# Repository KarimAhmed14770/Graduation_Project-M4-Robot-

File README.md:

"# Graduation_Project-M4-Robot-"

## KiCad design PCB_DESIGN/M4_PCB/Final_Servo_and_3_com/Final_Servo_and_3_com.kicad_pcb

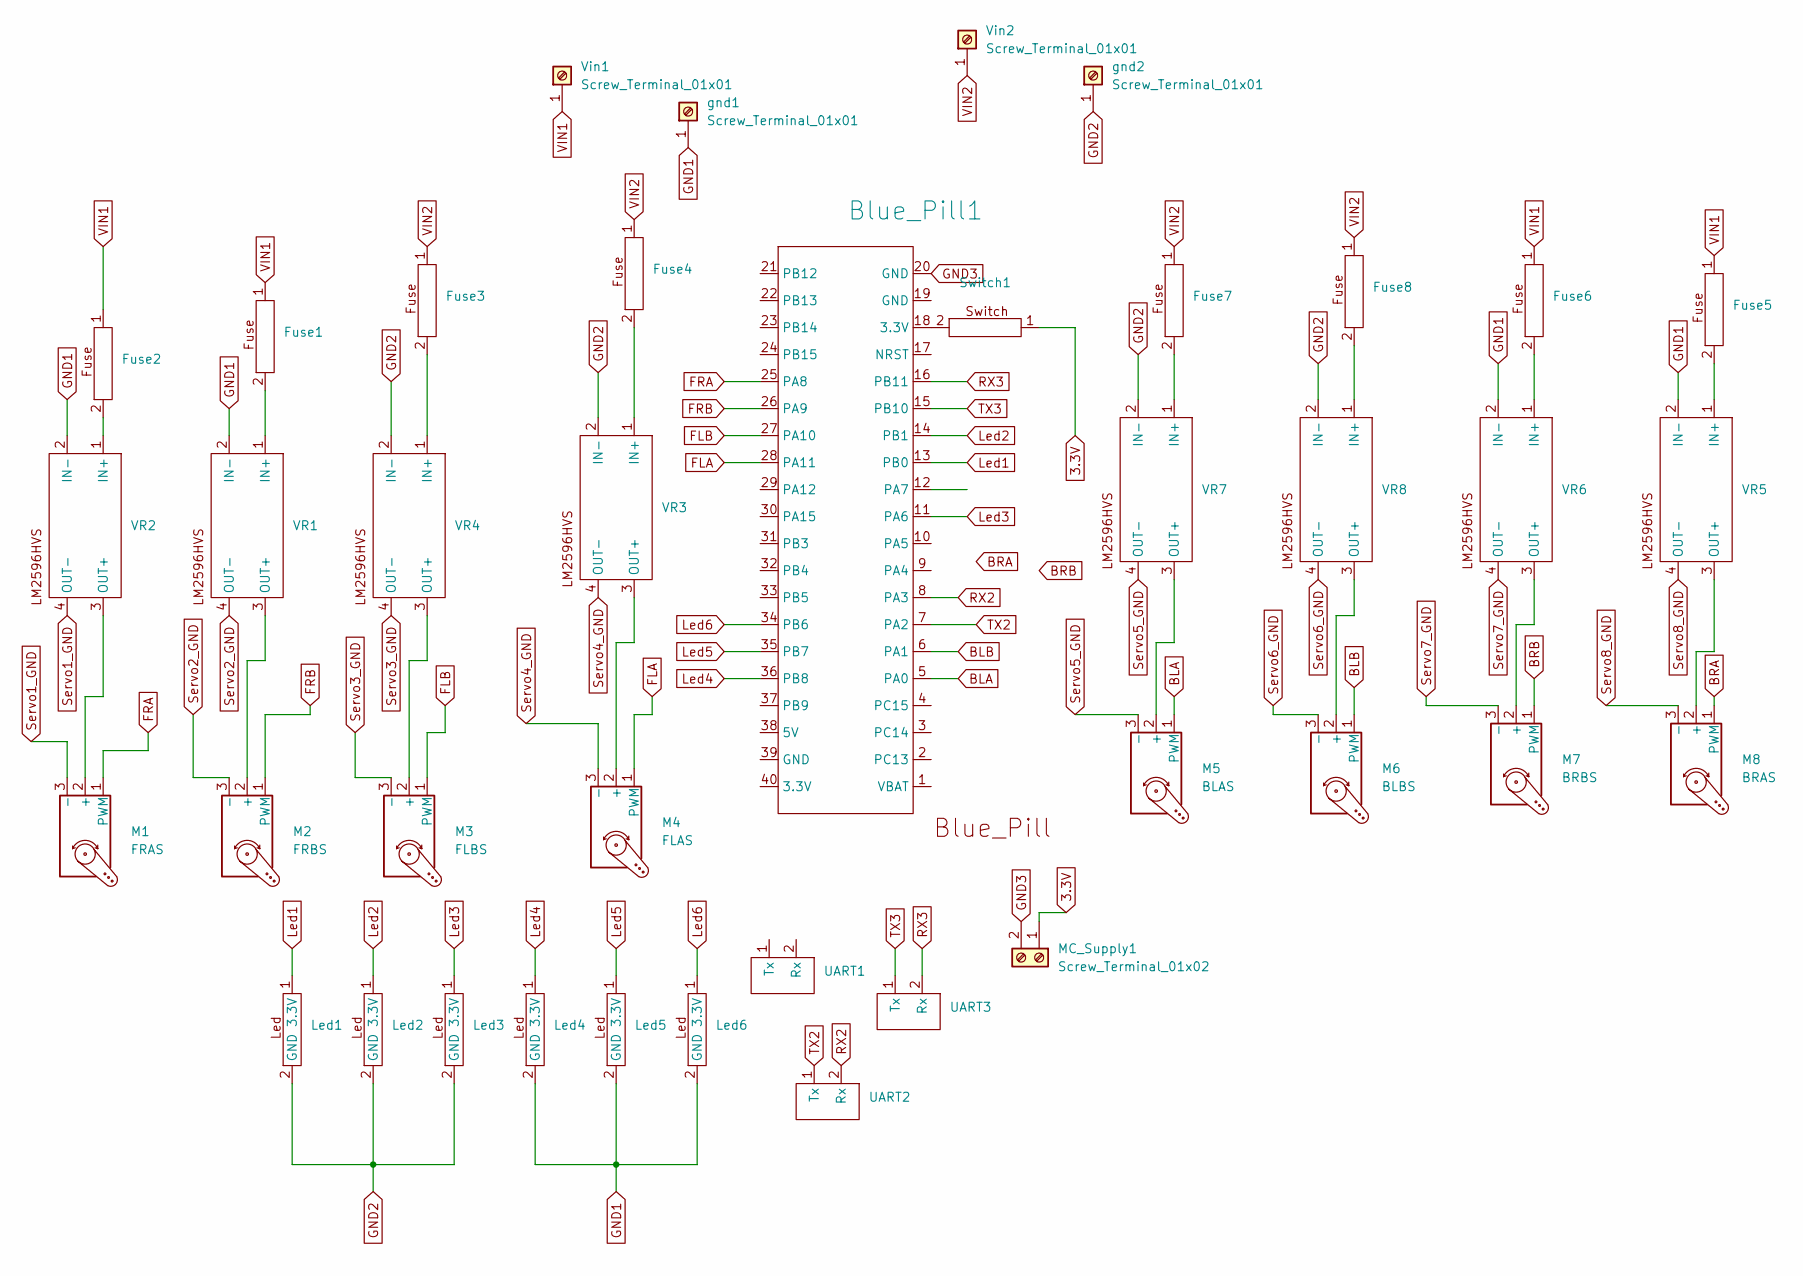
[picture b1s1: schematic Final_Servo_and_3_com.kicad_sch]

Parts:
Blue_Pill1: blue_pill
Fuse1, Fuse2, Fuse3, Fuse4, Fuse5, Fuse6, Fuse7, Fuse8: Fuse_Holder
Led1, Led2, Led3, Led4, Led5, Led6: LED
M1: FRAS; Servo
M2: FRBS; Servo
M3: FLBS; Servo
M4: FLAS; Servo
M5: BLAS; Servo
M6: BLBS; Servo
M7: BRBS; Servo
M8: BRAS; Servo
MC_Supply1: Screw_Terminal_01x02; Microcontrollers
Switch1: switch
UART1, UART2, UART3: communication
VR1, VR2, VR3, VR4, VR5, VR6, VR7, VR8: LM2596HVS
Vin1, Vin2: Screw_Terminal_01x01; one_terminal_VDD
gnd1, gnd2: Screw_Terminal_01x01; one_terminal_GND

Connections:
3.3V: MC_Supply1.1, Switch1.1
BLA: Blue_Pill1.5 (PA0), M5.1 (PWM)
BLB: Blue_Pill1.6 (PA1), M6.1 (PWM)
FLA: Blue_Pill1.28 (PA11), M4.1 (PWM)
FLB: Blue_Pill1.27 (PA10), M3.1 (PWM)
FRA: Blue_Pill1.25 (PA8), M1.1 (PWM)
FRB: Blue_Pill1.26 (PA9), M2.1 (PWM)
GND1: Led4.2 (GND), Led5.2 (GND), Led6.2 (GND), VR1.2 (IN-), VR2.2 (IN-), VR5.2 (IN-), VR6.2 (IN-), gnd1.1
GND2: Led1.2 (GND), Led2.2 (GND), Led3.2 (GND), VR3.2 (IN-), VR4.2 (IN-), VR7.2 (IN-), VR8.2 (IN-), gnd2.1
GND3: Blue_Pill1.20 (GND), MC_Supply1.2
Led1: Blue_Pill1.13 (PB0), Led1.1 (3.3V)
Led2: Blue_Pill1.14 (PB1), Led2.1 (3.3V)
Led3: Blue_Pill1.11 (PA6), Led3.1 (3.3V)
Led4: Blue_Pill1.36 (PB8), Led4.1 (3.3V)
Led5: Blue_Pill1.35 (PB7), Led5.1 (3.3V)
Led6: Blue_Pill1.34 (PB6), Led6.1 (3.3V)
unnamed: Blue_Pill1.18 (3.3V), Switch1.2
unnamed: M1.2 (+), VR2.3 (OUT+)
unnamed: M2.2 (+), VR1.3 (OUT+)
unnamed: M3.2 (+), VR4.3 (OUT+)
unnamed: M4.2 (+), VR3.3 (OUT+)
unnamed: M5.2 (+), VR7.3 (OUT+)
unnamed: M6.2 (+), VR8.3 (OUT+)
unnamed: M7.2 (+), VR6.3 (OUT+)
unnamed: M8.2 (+), VR5.3 (OUT+)
unnamed: Fuse1.2, VR1.1 (IN+)
unnamed: Fuse2.2, VR2.1 (IN+)
unnamed: Fuse4.2, VR3.1 (IN+)
unnamed: Fuse3.2, VR4.1 (IN+)
unnamed: Fuse5.2, VR5.1 (IN+)
unnamed: Fuse6.2, VR6.1 (IN+)
unnamed: Fuse7.2, VR7.1 (IN+)
unnamed: Fuse8.2, VR8.1 (IN+)
RX3: Blue_Pill1.16 (PB11), UART3.2 (Rx)
Servo1_GND: M1.3 (-), VR2.4 (OUT-)
Servo2_GND: M2.3 (-), VR1.4 (OUT-)
Servo3_GND: M3.3 (-), VR4.4 (OUT-)
Servo4_GND: M4.3 (-), VR3.4 (OUT-)
Servo5_GND: M5.3 (-), VR7.4 (OUT-)
Servo6_GND: M6.3 (-), VR8.4 (OUT-)
Servo7_GND: M7.3 (-), VR6.4 (OUT-)
Servo8_GND: M8.3 (-), VR5.4 (OUT-)
TX3: Blue_Pill1.15 (PB10), UART3.1 (Tx)
VIN1: Fuse1.1, Fuse2.1, Fuse5.1, Fuse6.1, Vin1.1
VIN2: Fuse3.1, Fuse4.1, Fuse7.1, Fuse8.1, Vin2.1

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
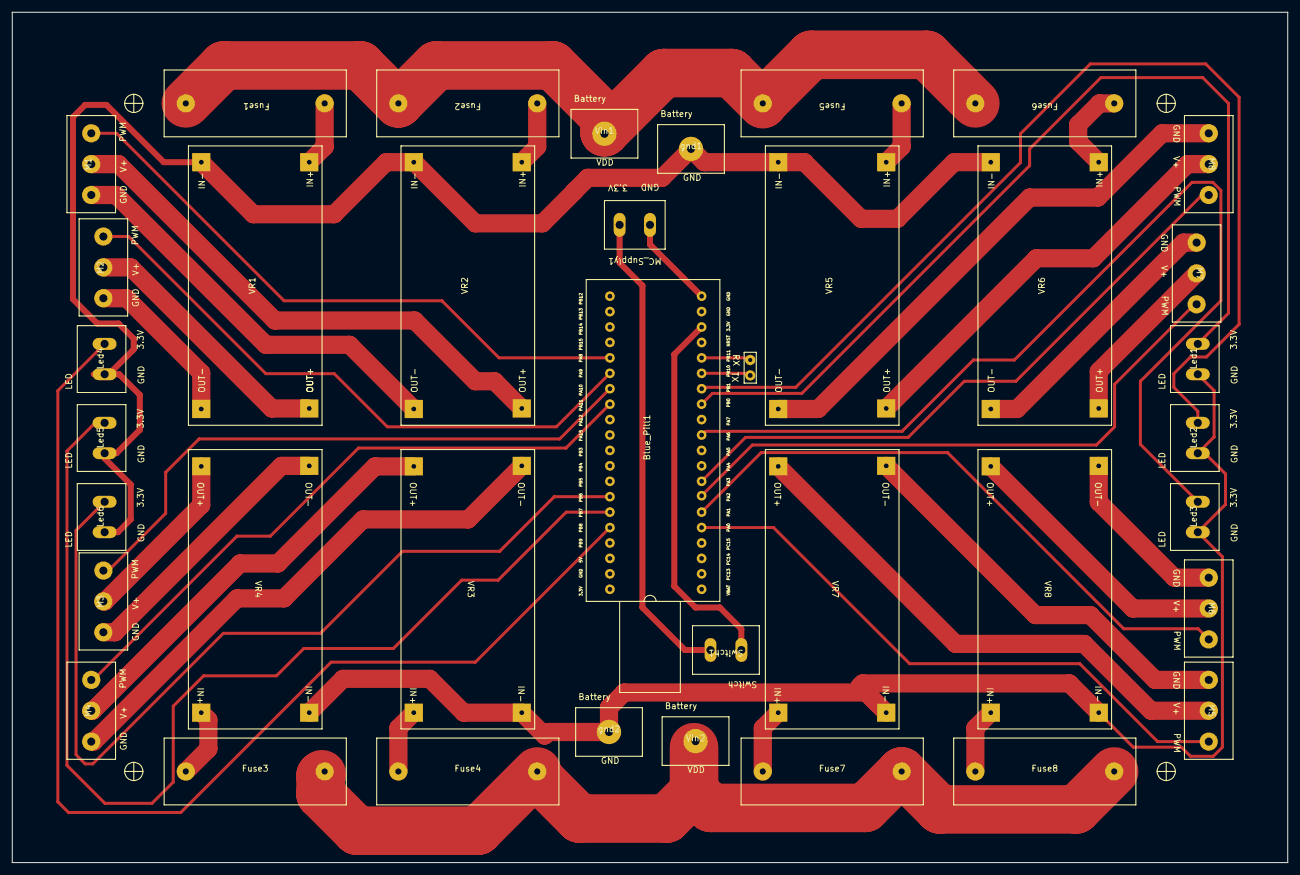
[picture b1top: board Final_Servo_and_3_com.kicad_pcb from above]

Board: 2 copper layers, 210.0 x 140.0 mm, 38 parts (0 on the bottom side), 47 nets.

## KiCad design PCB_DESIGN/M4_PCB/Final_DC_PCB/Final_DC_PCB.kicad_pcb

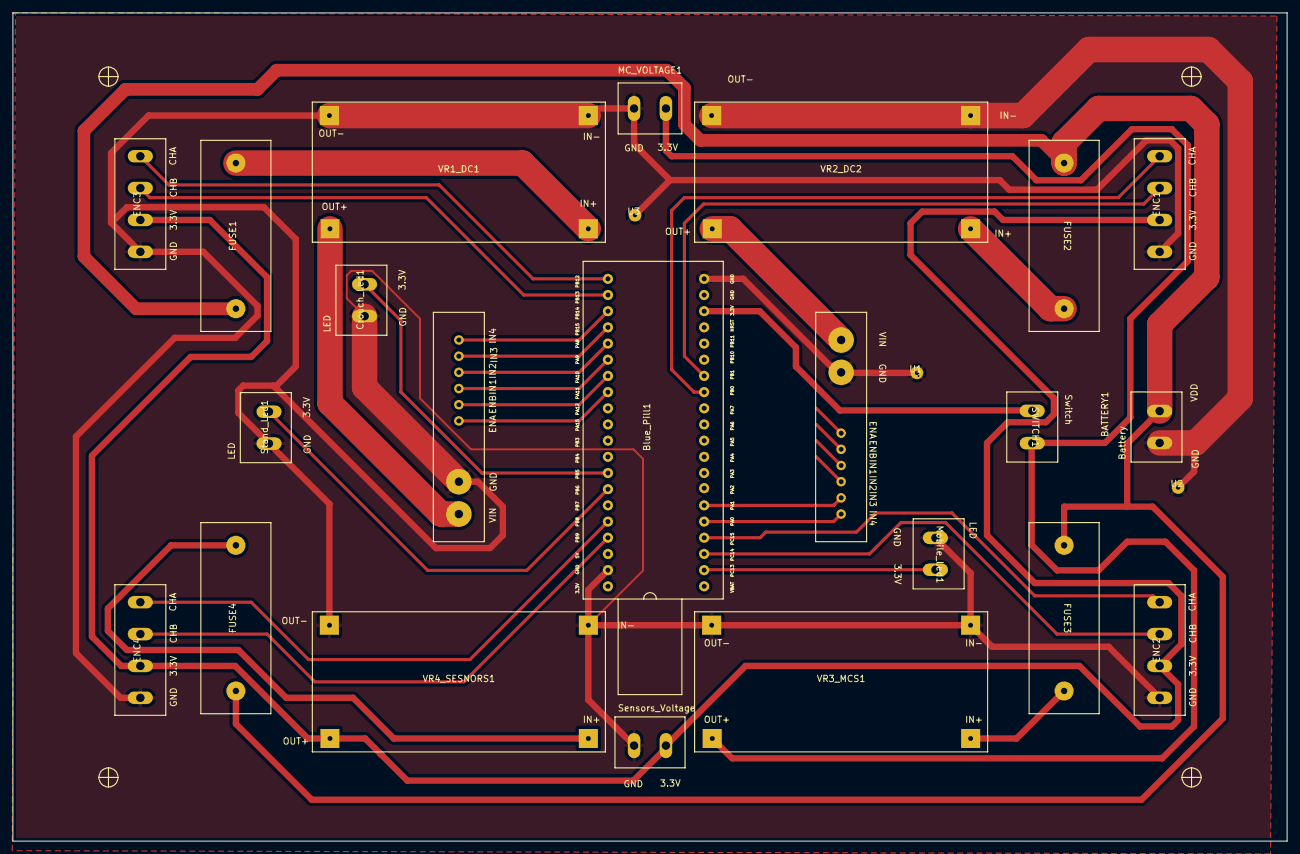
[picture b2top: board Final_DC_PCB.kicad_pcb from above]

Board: 2 copper layers, 200.0 x 130.0 mm, 25 parts (0 on the bottom side), 34 nets.

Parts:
BATTERY1: battery
Blue_Pill1: blue_pill
Crouch_Led1: LED
DRIVER1, DRIVER2: L298N
ENC1, ENC2, ENC3, ENC4: Encoder
FUSE1, FUSE2, FUSE3, FUSE4: Fuse_Holder
MC_VOLTAGE1: Microcontrollers
Mobile_Led1: LED
SENSORS_VOLTAGE1: sensors
SWITCH1: switch
Stand_Led1: LED
U1, U2, U3: pad
VR1_DC1, VR2_DC2, VR3_MCS1, VR4_SESNORS1: LM2596HVS

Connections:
3.3V_Sensors: ENC1.3 (E+), ENC2.3 (E+), ENC3.3 (E+), ENC4.3 (E+), SENSORS_VOLTAGE1.1 (3.3V), VR4_SESNORS1.3 (OUT+)
Back_Driver_12VIN: DRIVER2.1 (Vin), VR2_DC2.3 (OUT+)
Blue_Pill3.3V: MC_VOLTAGE1.1 (3.3V), SWITCH1.1, VR3_MCS1.3 (OUT+)
Crouch_Led_3.3V: Blue_Pill1.33 (PB5), Crouch_Led1.1 (3.3V)
Front_Driver_12VIN: DRIVER1.1 (Vin), VR1_DC1.3 (OUT+)
GND: BATTERY1.2 (GND), Blue_Pill1.20 (GND), Blue_Pill1.39 (GND), Crouch_Led1.2 (GND), DRIVER1.2 (GND), DRIVER2.2 (GND), ENC1.4 (E-), ENC2.4 (E-), ENC3.4 (E-), ENC4.4 (E-), MC_VOLTAGE1.2 (GND), Mobile_Led1.2 (GND), SENSORS_VOLTAGE1.2 (GND), Stand_Led1.2 (GND), U1.1 (pad), U2.1 (pad), U3.1 (pad), VR1_DC1.2 (IN-), VR2_DC2.2 (IN-), VR3_MCS1.2 (IN-), VR4_SESNORS1.2 (IN-)
Mobile_Led_3.3V: Blue_Pill1.2 (PC13), Mobile_Led1.1 (3.3V)
unnamed: Blue_Pill1.18 (3.3V), SWITCH1.2
unnamed: Blue_Pill1.5 (PA0), DRIVER2.8 (IN4)
unnamed: Blue_Pill1.6 (PA1), DRIVER2.7 (IN3)
unnamed: Blue_Pill1.9 (PA4), DRIVER2.6 (IN2)
unnamed: Blue_Pill1.10 (PA5), DRIVER2.5 (IN1)
unnamed: Blue_Pill1.11 (PA6), DRIVER2.9 (ENB)
unnamed: Blue_Pill1.12 (PA7), DRIVER2.4 (ENA)
unnamed: Blue_Pill1.25 (PA8), DRIVER1.6 (IN2)
unnamed: Blue_Pill1.26 (PA9), DRIVER1.5 (IN1)
unnamed: Blue_Pill1.27 (PA10), DRIVER1.9 (ENB)
unnamed: Blue_Pill1.28 (PA11), DRIVER1.4 (ENA)
unnamed: Blue_Pill1.13 (PB0), ENC1.1 (CHA)
unnamed: Blue_Pill1.14 (PB1), ENC1.2 (CHB)
unnamed: Blue_Pill1.36 (PB8), ENC4.1 (CHA)
unnamed: Blue_Pill1.37 (PB9), ENC4.2 (CHB)
unnamed: Blue_Pill1.21 (PB12), ENC3.1 (CHA)
unnamed: Blue_Pill1.22 (PB13), ENC3.2 (CHB)
unnamed: Blue_Pill1.23 (PB14), DRIVER1.8 (IN4)
unnamed: Blue_Pill1.24 (PB15), DRIVER1.7 (IN3)
unnamed: Blue_Pill1.3 (PC14), ENC2.2 (CHB)
unnamed: Blue_Pill1.4 (PC15), ENC2.1 (CHA)
unnamed: FUSE1.1, VR1_DC1.1 (IN+)
unnamed: FUSE2.1, VR2_DC2.1 (IN+)
unnamed: FUSE3.1, VR3_MCS1.1 (IN+)
unnamed: FUSE4.1, VR4_SESNORS1.1 (IN+)
Stand_Led_3.3V: Blue_Pill1.34 (PB6), Stand_Led1.1 (3.3V)
VBAT: BATTERY1.1 (VDD), FUSE1.2, FUSE2.2, FUSE3.2, FUSE4.2

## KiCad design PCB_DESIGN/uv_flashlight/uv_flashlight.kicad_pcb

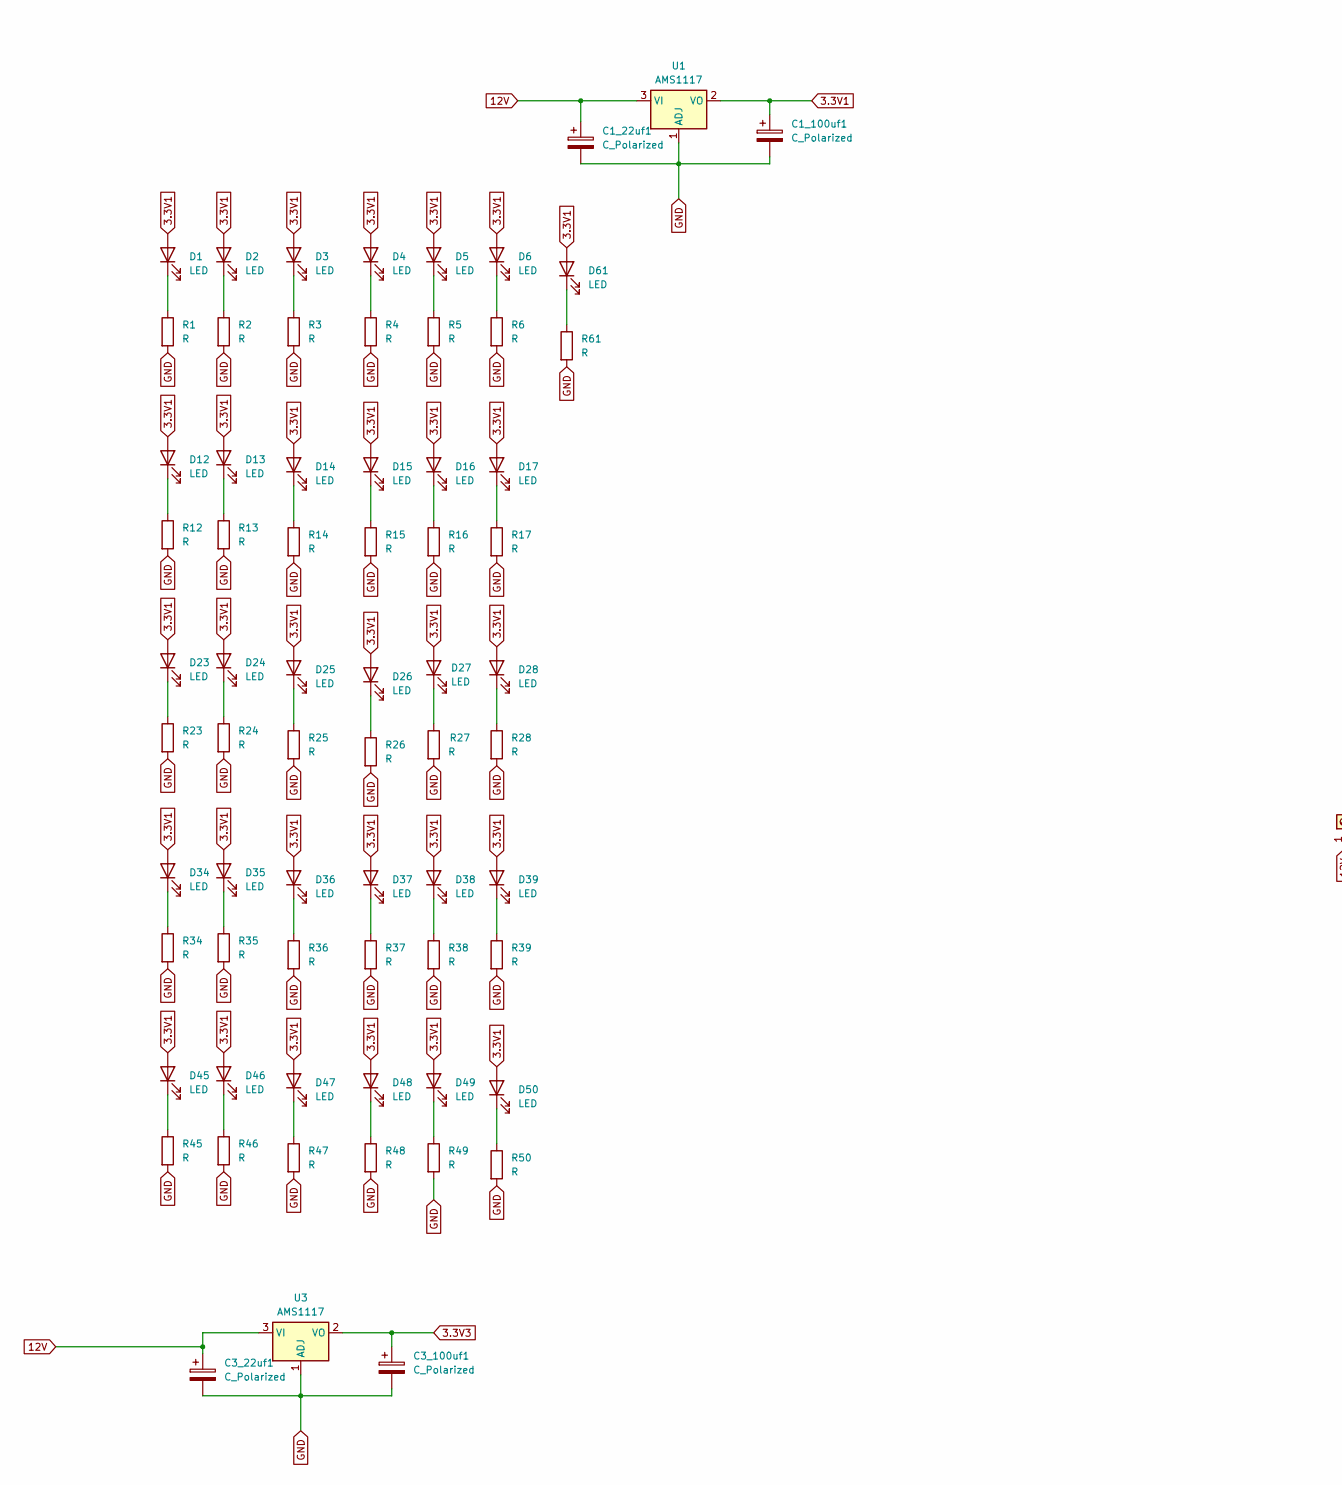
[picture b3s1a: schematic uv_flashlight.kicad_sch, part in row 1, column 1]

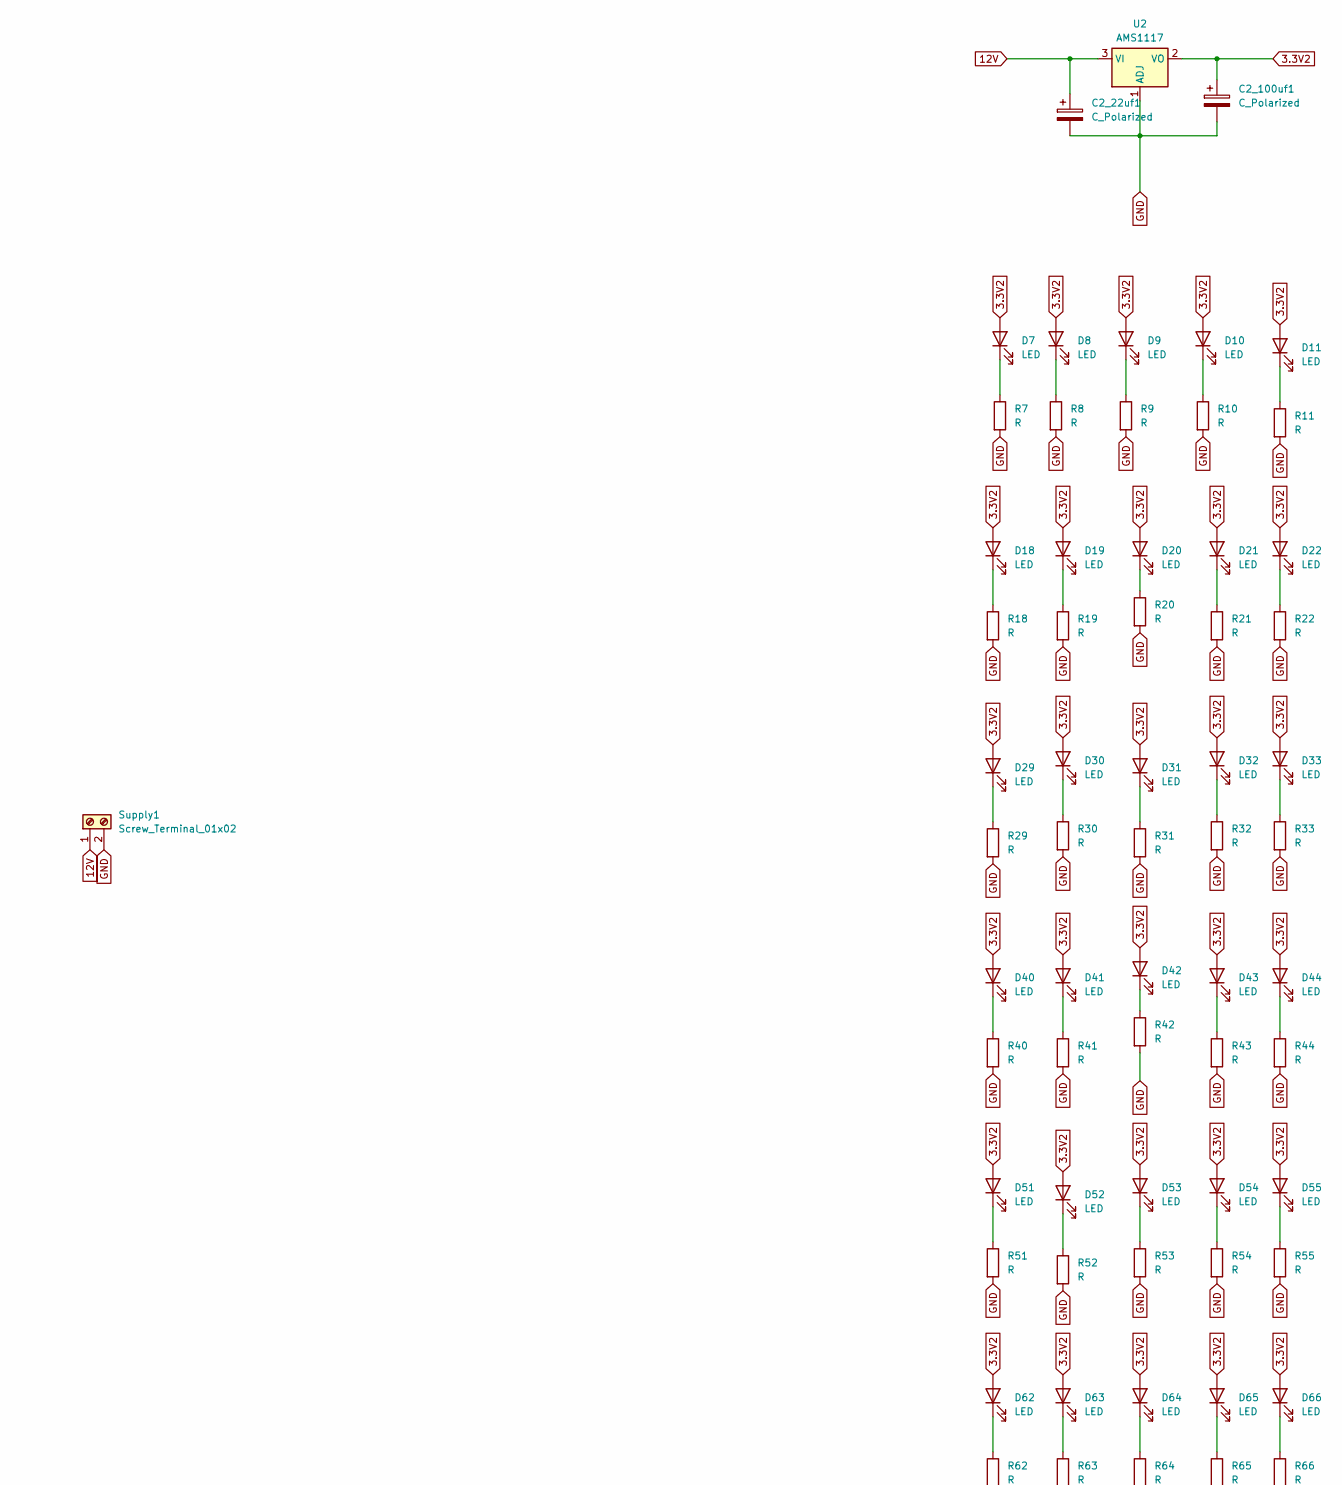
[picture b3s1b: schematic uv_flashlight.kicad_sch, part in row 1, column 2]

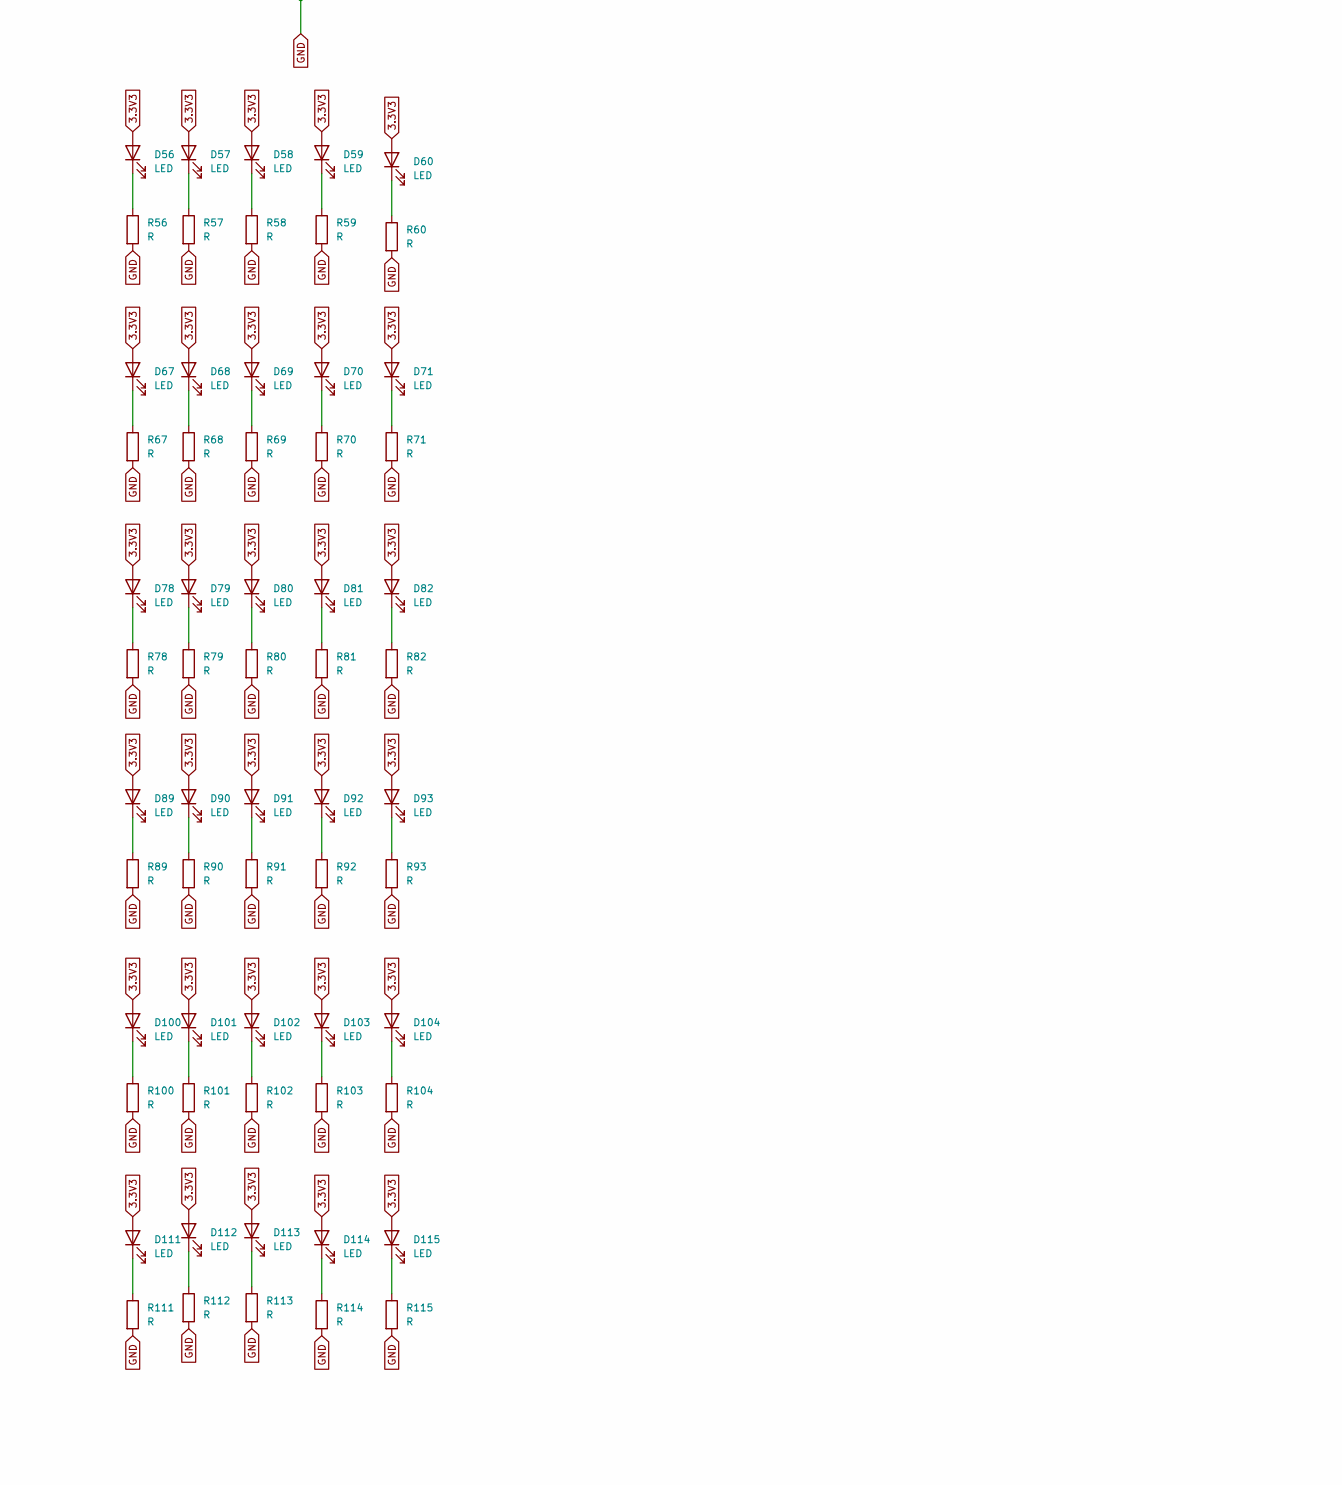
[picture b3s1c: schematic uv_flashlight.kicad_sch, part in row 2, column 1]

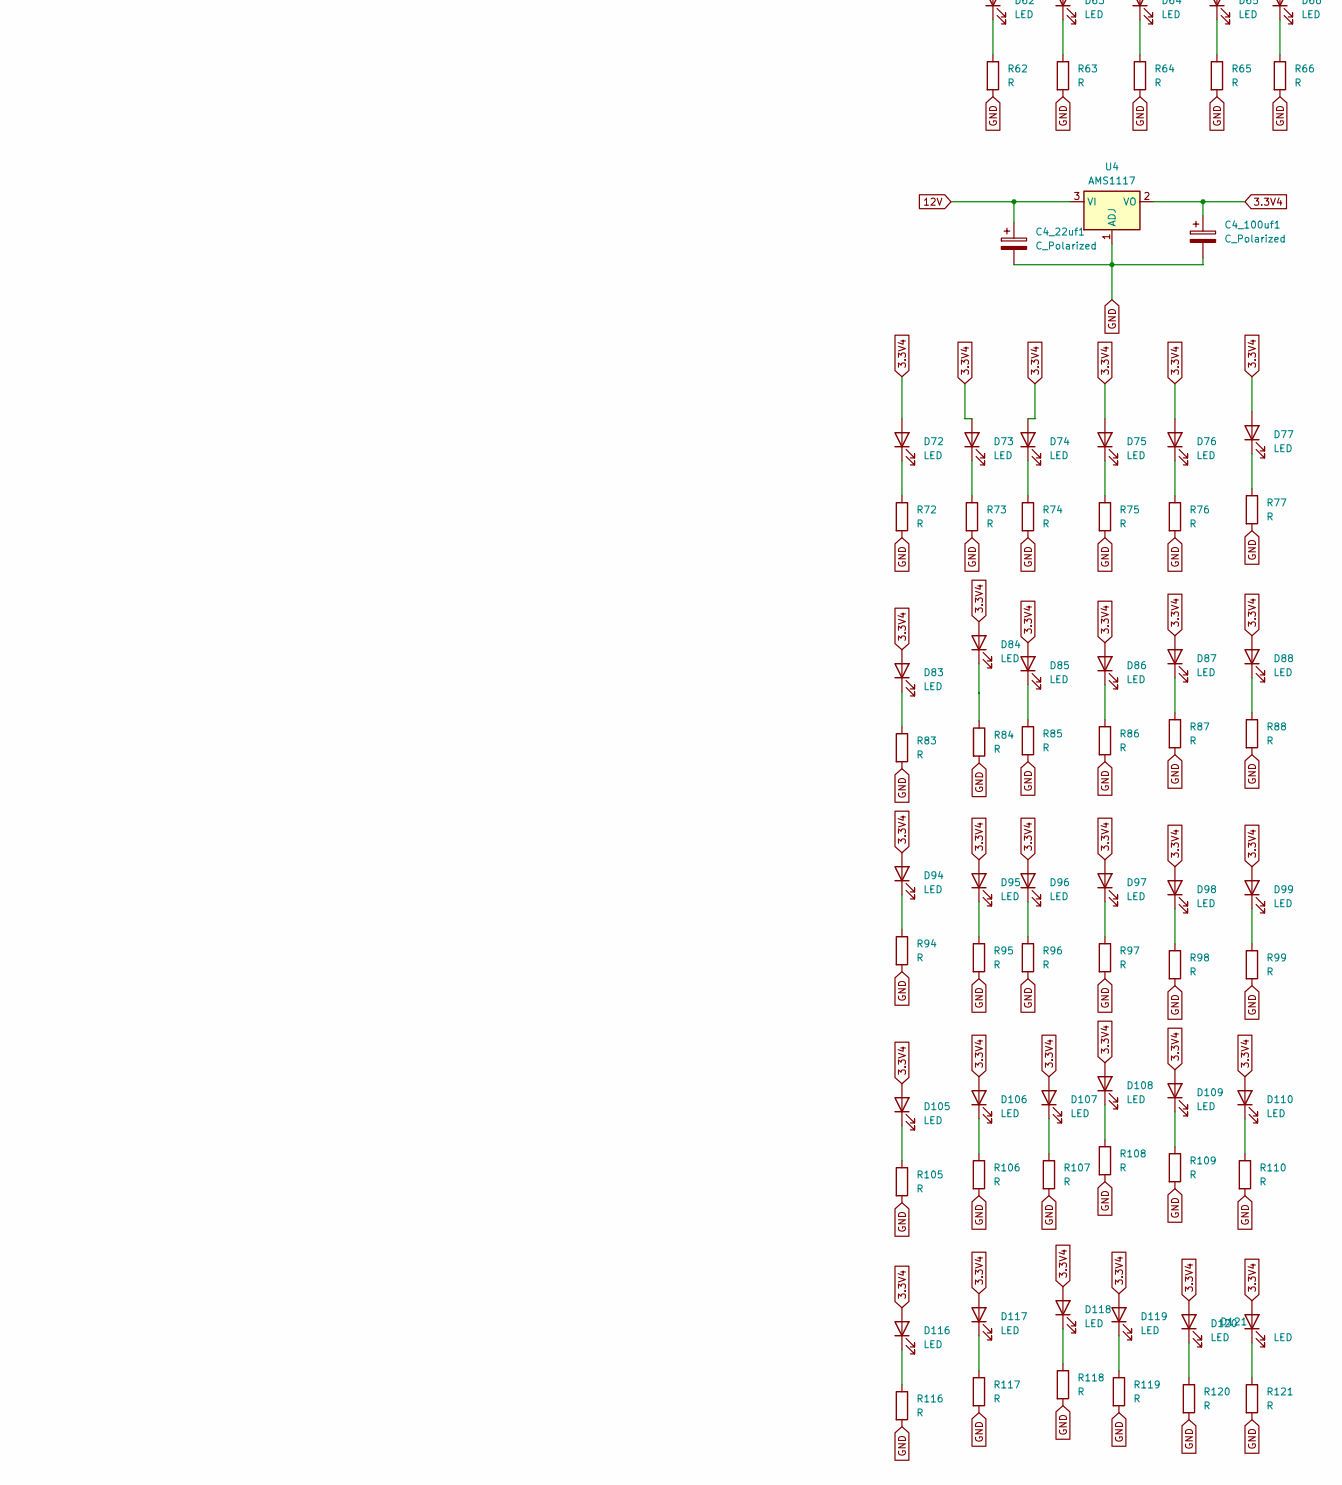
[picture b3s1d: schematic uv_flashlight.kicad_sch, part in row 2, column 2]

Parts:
C1_22uf1, C1_100uf1, C2_22uf1, C2_100uf1, C3_22uf1, C3_100uf1, C4_22uf1, C4_100uf1: C_Polarized; CP_Radial_D5.0mm_P2.50mm
D1, D2, D3, D4, D5, D6, D7, D8, D9, D10, D11, D12, D13, D14, D15, D16, D17, D18, D19, D20, D21, D22, D23, D24, D25, D26, D27, D28, D29, D30, D31, D32, D33, D34, D35, D36, D37, D38, D39, D40, D41, D42, D43, D44, D45, D46, D47, D48, D49, D50, D51, D52, D53, D54, D55, D56, D57, D58, D59, D60, D61, D62, D63, D64, D65, D66, D67, D68, D69, D70, D71, D72, D73, D74, D75, D76, D77, D78, D79, D80, D81, D82, D83, D84, D85, D86, D87, D88, D89, D90, D91, D92, D93, D94, D95, D96, D97, D98, D99, D100, D101, D102, D103, D104, D105, D106, D107, D108, D109, D110, D111, D112, D113, D114, D115, D116, D117, D118, D119, D120, D121: LED; LED_D5.0mm
R1, R2, R3, R4, R5, R6, R7, R8, R9, R10, R11, R12, R13, R14, R15, R16, R17, R18, R19, R20, R21, R22, R23, R24, R25, R26, R27, R28, R29, R30, R31, R32, R33, R34, R35, R36, R37, R38, R39, R40, R41, R42, R43, R44, R45, R46, R47, R48, R49, R50, R51, R52, R53, R54, R55, R56, R57, R58, R59, R60, R61, R62, R63, R64, R65, R66, R67, R68, R69, R70, R71, R72, R73, R74, R75, R76, R77, R78, R79, R80, R81, R82, R83, R84, R85, R86, R87, R88, R89, R90, R91, R92, R93, R94, R95, R96, R97, R98, R99, R100, R101, R102, R103, R104, R105, R106, R107, R108, R109, R110, R111, R112, R113, R114, R115, R116, R117, R118, R119, R120, R121: R; R_Axial_DIN0204_L3.6mm_D1.6mm_P2.54mm_Vertical
Supply1: Screw_Terminal_01x02; TerminalBlock_bornier-2_P5.08mm
U1, U2, U3, U4: AMS1117; SOT-223-3_TabPin2

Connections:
3.3V1: C1_100uf1.1, D1.2 (A), D2.2 (A), D3.2 (A), D4.2 (A), D5.2 (A), D6.2 (A), D12.2 (A), D13.2 (A), D14.2 (A), D15.2 (A), D16.2 (A), D17.2 (A), D23.2 (A), D24.2 (A), D25.2 (A), D26.2 (A), D27.2 (A), D28.2 (A), D34.2 (A), D35.2 (A), D36.2 (A), D37.2 (A), D38.2 (A), D39.2 (A), D45.2 (A), D46.2 (A), D47.2 (A), D48.2 (A), D49.2 (A), D50.2 (A), D61.2 (A), U1.2 (VO)
3.3V2: C2_100uf1.1, D7.2 (A), D8.2 (A), D9.2 (A), D10.2 (A), D11.2 (A), D18.2 (A), D19.2 (A), D20.2 (A), D21.2 (A), D22.2 (A), D29.2 (A), D30.2 (A), D31.2 (A), D32.2 (A), D33.2 (A), D40.2 (A), D41.2 (A), D42.2 (A), D43.2 (A), D44.2 (A), D51.2 (A), D52.2 (A), D53.2 (A), D54.2 (A), D55.2 (A), D62.2 (A), D63.2 (A), D64.2 (A), D65.2 (A), D66.2 (A), U2.2 (VO)
3.3V3: C3_100uf1.1, D56.2 (A), D57.2 (A), D58.2 (A), D59.2 (A), D60.2 (A), D67.2 (A), D68.2 (A), D69.2 (A), D70.2 (A), D71.2 (A), D78.2 (A), D79.2 (A), D80.2 (A), D81.2 (A), D82.2 (A), D89.2 (A), D90.2 (A), D91.2 (A), D92.2 (A), D93.2 (A), D100.2 (A), D101.2 (A), D102.2 (A), D103.2 (A), D104.2 (A), D111.2 (A), D112.2 (A), D113.2 (A), D114.2 (A), D115.2 (A), U3.2 (VO)
3.3V4: C4_100uf1.1, D72.2 (A), D73.2 (A), D74.2 (A), D75.2 (A), D76.2 (A), D77.2 (A), D83.2 (A), D84.2 (A), D85.2 (A), D86.2 (A), D87.2 (A), D88.2 (A), D94.2 (A), D95.2 (A), D96.2 (A), D97.2 (A), D98.2 (A), D99.2 (A), D105.2 (A), D106.2 (A), D107.2 (A), D108.2 (A), D109.2 (A), D110.2 (A), D116.2 (A), D117.2 (A), D118.2 (A), D119.2 (A), D120.2 (A), D121.2 (A), U4.2 (VO)
12V: C1_22uf1.1, C2_22uf1.1, C3_22uf1.1, C4_22uf1.1, Supply1.1, U1.3 (VI), U2.3 (VI), U3.3 (VI), U4.3 (VI)
GND: C1_22uf1.2, C1_100uf1.2, C2_22uf1.2, C2_100uf1.2, C3_22uf1.2, C3_100uf1.2, C4_22uf1.2, C4_100uf1.2, R1.2, R2.2, R3.2, R4.2, R5.2, R6.2, R7.2, R8.2, R9.2, R10.2, R11.2, R12.2, R13.2, R14.2, R15.2, R16.2, R17.2, R18.2, R19.2, R20.2, R21.2, R22.2, R23.2, R24.2, R25.2, R26.2, R27.2, R28.2, R29.2, R30.2, R31.2, R32.2, R33.2, R34.2, R35.2, R36.2, R37.2, R38.2, R39.2, R40.2, R41.2, R42.2, R43.2, R44.2, R45.2, R46.2, R47.2, R48.2, R49.2, R50.2, R51.2, R52.2, R53.2, R54.2, R55.2, R56.2, R57.2, R58.2, R59.2, R60.2, R61.2, R62.2, R63.2, R64.2, R65.2, R66.2, R67.2, R68.2, R69.2, R70.2, R71.2, R72.2, R73.2, R74.2, R75.2, R76.2, R77.2, R78.2, R79.2, R80.2, R81.2, R82.2, R83.2, R84.2, R85.2, R86.2, R87.2, R88.2, R89.2, R90.2, R91.2, R92.2, R93.2, R94.2, R95.2, R96.2, R97.2, R98.2, R99.2, R100.2, R101.2, R102.2, R103.2, R104.2, R105.2, R106.2, R107.2, R108.2, R109.2, R110.2, R111.2, R112.2, R113.2, R114.2, R115.2, R116.2, R117.2, R118.2, R119.2, R120.2, R121.2, Supply1.2, U1.1 (ADJ), U2.1 (ADJ), U3.1 (ADJ), U4.1 (ADJ)
unnamed: D1.1 (K), R1.1
unnamed: D2.1 (K), R2.1
unnamed: D3.1 (K), R3.1
unnamed: D4.1 (K), R4.1
unnamed: D5.1 (K), R5.1
unnamed: D6.1 (K), R6.1
unnamed: D7.1 (K), R7.1
unnamed: D8.1 (K), R8.1
unnamed: D9.1 (K), R9.1
unnamed: D10.1 (K), R10.1
unnamed: D11.1 (K), R11.1
unnamed: D12.1 (K), R12.1
unnamed: D13.1 (K), R13.1
unnamed: D14.1 (K), R14.1
unnamed: D15.1 (K), R15.1
unnamed: D16.1 (K), R16.1
unnamed: D17.1 (K), R17.1
unnamed: D18.1 (K), R18.1
unnamed: D19.1 (K), R19.1
unnamed: D20.1 (K), R20.1
unnamed: D21.1 (K), R21.1
unnamed: D22.1 (K), R22.1
unnamed: D23.1 (K), R23.1
unnamed: D24.1 (K), R24.1
unnamed: D25.1 (K), R25.1
unnamed: D26.1 (K), R26.1
unnamed: D27.1 (K), R27.1
unnamed: D28.1 (K), R28.1
unnamed: D29.1 (K), R29.1
unnamed: D30.1 (K), R30.1
unnamed: D31.1 (K), R31.1
unnamed: D32.1 (K), R32.1
unnamed: D33.1 (K), R33.1
unnamed: D34.1 (K), R34.1
unnamed: D35.1 (K), R35.1
unnamed: D36.1 (K), R36.1
unnamed: D37.1 (K), R37.1
unnamed: D38.1 (K), R38.1
unnamed: D39.1 (K), R39.1
unnamed: D40.1 (K), R40.1
unnamed: D41.1 (K), R41.1
unnamed: D42.1 (K), R42.1
unnamed: D43.1 (K), R43.1
unnamed: D44.1 (K), R44.1
unnamed: D45.1 (K), R45.1
unnamed: D46.1 (K), R46.1
unnamed: D47.1 (K), R47.1
unnamed: D48.1 (K), R48.1
unnamed: D49.1 (K), R49.1
unnamed: D50.1 (K), R50.1
unnamed: D51.1 (K), R51.1
unnamed: D52.1 (K), R52.1
unnamed: D53.1 (K), R53.1
unnamed: D54.1 (K), R54.1
unnamed: D55.1 (K), R55.1
unnamed: D56.1 (K), R56.1
unnamed: D57.1 (K), R57.1
unnamed: D58.1 (K), R58.1
unnamed: D59.1 (K), R59.1
unnamed: D60.1 (K), R60.1
unnamed: D61.1 (K), R61.1
unnamed: D62.1 (K), R62.1
unnamed: D63.1 (K), R63.1
unnamed: D64.1 (K), R64.1
unnamed: D65.1 (K), R65.1
unnamed: D66.1 (K), R66.1
unnamed: D67.1 (K), R67.1
unnamed: D68.1 (K), R68.1
unnamed: D69.1 (K), R69.1
unnamed: D70.1 (K), R70.1
unnamed: D71.1 (K), R71.1
unnamed: D72.1 (K), R72.1
unnamed: D73.1 (K), R73.1
unnamed: D74.1 (K), R74.1
unnamed: D75.1 (K), R75.1
unnamed: D76.1 (K), R76.1
unnamed: D77.1 (K), R77.1
unnamed: D78.1 (K), R78.1
unnamed: D79.1 (K), R79.1
unnamed: D80.1 (K), R80.1
unnamed: D81.1 (K), R81.1
unnamed: D82.1 (K), R82.1
unnamed: D83.1 (K), R83.1
unnamed: D84.1 (K), R84.1
unnamed: D85.1 (K), R85.1
unnamed: D86.1 (K), R86.1
unnamed: D87.1 (K), R87.1
unnamed: D88.1 (K), R88.1
unnamed: D89.1 (K), R89.1
unnamed: D90.1 (K), R90.1
unnamed: D91.1 (K), R91.1
unnamed: D92.1 (K), R92.1
unnamed: D93.1 (K), R93.1
unnamed: D94.1 (K), R94.1
unnamed: D95.1 (K), R95.1
unnamed: D96.1 (K), R96.1
unnamed: D97.1 (K), R97.1
unnamed: D98.1 (K), R98.1
unnamed: D99.1 (K), R99.1
unnamed: D100.1 (K), R100.1
unnamed: D101.1 (K), R101.1
unnamed: D102.1 (K), R102.1
unnamed: D103.1 (K), R103.1
unnamed: D104.1 (K), R104.1
unnamed: D105.1 (K), R105.1
unnamed: D106.1 (K), R106.1
unnamed: D107.1 (K), R107.1
unnamed: D108.1 (K), R108.1
unnamed: D109.1 (K), R109.1
unnamed: D110.1 (K), R110.1
unnamed: D111.1 (K), R111.1
unnamed: D112.1 (K), R112.1
unnamed: D113.1 (K), R113.1
unnamed: D114.1 (K), R114.1
unnamed: D115.1 (K), R115.1
unnamed: D116.1 (K), R116.1
unnamed: D117.1 (K), R117.1
unnamed: D118.1 (K), R118.1
unnamed: D119.1 (K), R119.1
unnamed: D120.1 (K), R120.1
unnamed: D121.1 (K), R121.1

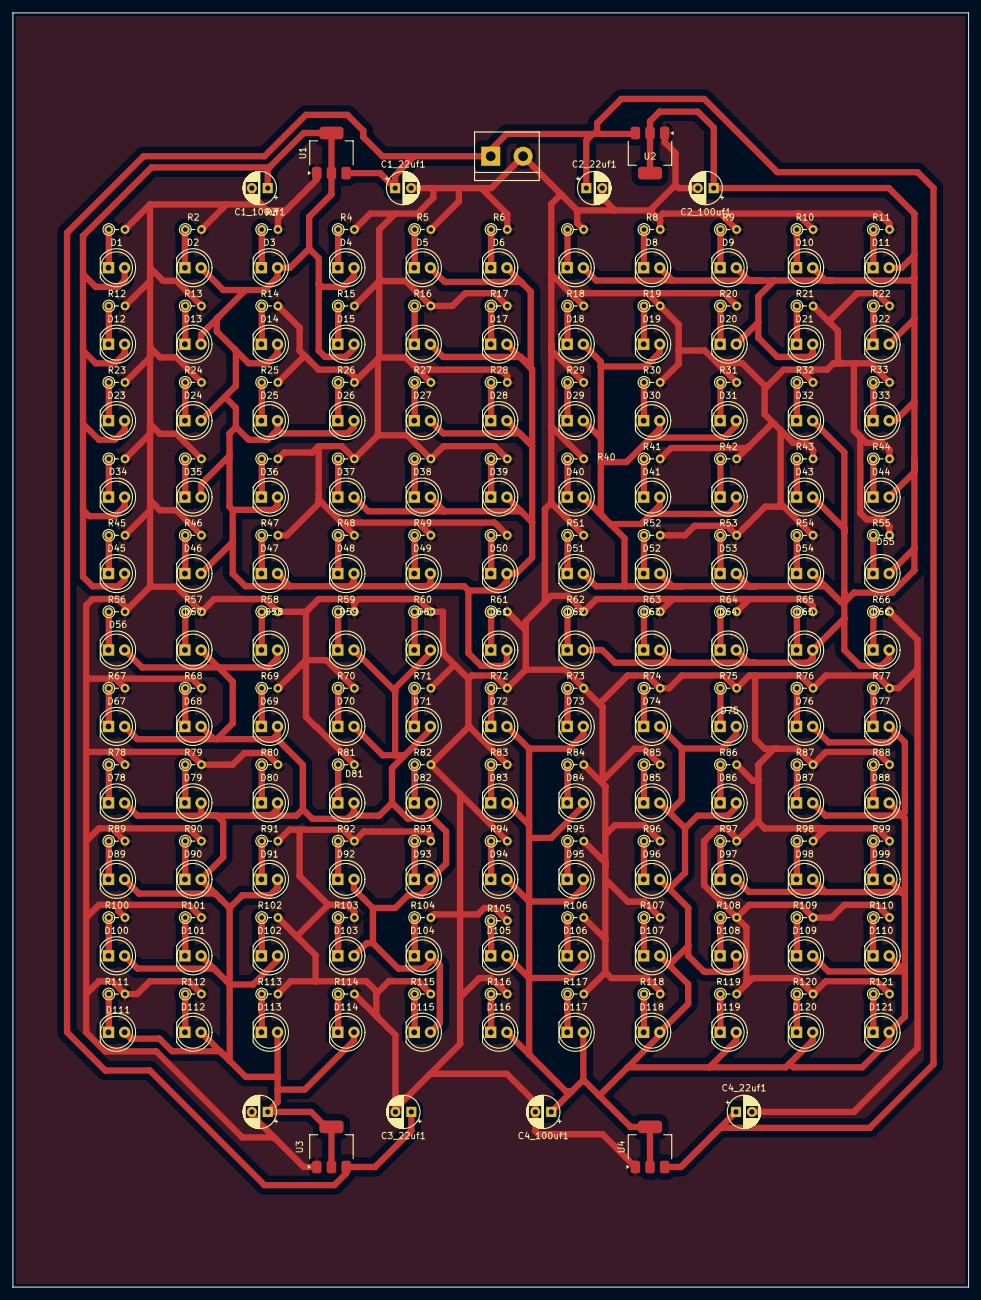
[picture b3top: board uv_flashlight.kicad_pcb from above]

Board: 2 copper layers, 150.0 x 200.0 mm, 255 parts (0 on the bottom side), 127 nets.

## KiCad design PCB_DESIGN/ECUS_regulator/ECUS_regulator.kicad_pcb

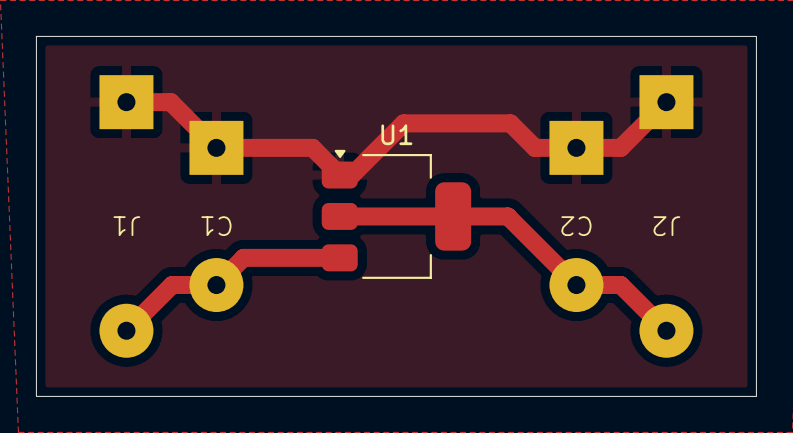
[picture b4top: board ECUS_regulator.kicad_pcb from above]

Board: 2 copper layers, 40.0 x 20.0 mm, 5 parts (0 on the bottom side), 3 nets.

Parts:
C1, C2: C_Polarized; two_pads_7.62
J1, J2: Screw_Terminal_01x02; regulator_pads
U1: AMS1117-3.3; SOT-223-3_TabPin2

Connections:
Earth: C1.3, C2.2, J1.2, J2.2, U1.1 (GND)
unnamed: C1.1, J1.1, U1.3 (VI)
unnamed: C2.1, J2.1, U1.2 (VO)
